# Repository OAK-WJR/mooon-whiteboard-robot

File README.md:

# MOOON: a robot that drives on a vertical whiteboard

MOOON (the project folder is called WhiteBoardBot) is a small robot with three
omni wheels that holds itself to a **vertical magnetic whiteboard** with
magnets. It can hold still against gravity, sweep the whole board in lanes,
find ink with a camera and erase it, and draw with a pen. It runs on circuit
boards I designed and on ESP32-C6 firmware. A phone camera facing the board
measures where the robot really is and sends corrections over Wi-Fi.

*2026-10-27: the robot from above, on the purple base board (v2.6) that I
designed.*

> This repository keeps the real git history of the project from June 2026
> (when it moved into git) to today, filtered for review: raw logs, videos,
> vendor models and design backups were removed from every commit, and the
> final commit adds my uncommitted work from Oct 28–31, 2026. The Feb–Apr 2026
> work (v1 board, first chassis) appears only as images and netlists. The
> unfiltered repository, with about 1 GB of raw logs and videos, stays private.

## Demo

*2026-10-26: full-board coverage run on a 35 × 23 in whiteboard (writable
area 33.5 × 21.5 in), 4× speed. Red: path measured by the camera. Blue:
planned area. 13 lanes in 96.6 s; it came back to its start within 0.2 mm.*

| Before erasing | After erasing | Drawing "67" |
|---|---|---|
|  |  |  |
| 2026-10-28 22:35: 130 cm² of ink | 2026-10-28 ≈22:40: board clean | 2026-10-31: one continuous pen line |

Video: the MOOON part of the video in my MIT Maker Portfolio shows the erase
run and the "67" drawing. Raw videos are not stored in this repository.

## How it works

```
 iPhone camera (Continuity Camera) ─> Mac: OpenCV finds 4 red corner tapes
                                     and the robot's LCD beacon
                                          │ position fixes over Wi-Fi
                                          ▼
 ┌────────────────────────── robot ──────────────────────────┐
 │ ESP32-C6-LCD-1.47 module      <- c6_wall firmware          │
 │   └─ adapter PCB (v2, my design)                           │
 │        └─ base PCB (v2.6, my design): 3 H-bridges, 2S LiPo │
 │             └─ 3 N20 gearmotors with encoders,             │
 │                38 mm omni wheels at 120°, magnets          │
 └────────────────────────────────────────────────────────────┘
```

- **Holding on the wall.** Each wheel is a position servo. The integral term
  is never reset, because it holds the torque that keeps the robot up against
  gravity. When idle or after a fault, the motor drivers brake.
  ([`c6_wall/include/wbb_core.h`](c6_wall/include/wbb_core.h))
- **Slip.** The wheels slip on the glossy board, and the encoders cannot see
  that. Camera measurements gave a slip factor for each direction, and the
  firmware corrects its odometry with them.
- **Camera referee.** Four red tapes give the board's corners; the robot's LCD
  shows a cyan/magenta beacon that gives its position and heading. Each fix is
  matched to the robot's odometry history to cancel the camera delay.
  ([`c6_wall/tools/vision.py`](c6_wall/tools/vision.py))
- **Erasing.** The eraser is the felt under the middle magnet. The camera
  finds the ink, the planner covers it with left-right lanes 1.6 cm apart, and
  the robot repeats until nothing is left, then does a fine wipe.
  ([`c6_wall/tools/clean_dirty.py`](c6_wall/tools/clean_dirty.py))
- **Drawing.** The pen cannot lift, so "67" is one continuous path of 30
  points, driven with live camera corrections.
  ([`c6_wall/tools/draw_digits.py`](c6_wall/tools/draw_digits.py))

More detail and the full timeline of what failed and what changed:
[`docs/design-history/`](docs/design-history/),
[`hardware/README.md`](hardware/README.md),
[`c6_wall/README.md`](c6_wall/README.md).

## Build and run

**Hardware needed:** the robot (Waveshare ESP32-C6-LCD-1.47, my adapter v2 and
base v2.6 boards, 3 N20 encoder gearmotors, 38 mm omni wheels, magnets, 2S
LiPo), a magnetic whiteboard with red tape on its four corners, a Mac with an
iPhone as Continuity Camera for the camera tools, and a USB-C cable for the
first flash.

```bash
# PlatformIO needs Python 3.10 or newer (macOS's built-in python3 is 3.9).
# The first build downloads the ESP32 toolchain into ./.platformio
python3.13 -m venv .venv && .venv/bin/pip install platformio
cd c6_wall
../.venv/bin/pio run                  # build the firmware
../.venv/bin/pio run -t upload        # first install over USB
python3 tools/ota.py                  # later updates over Wi-Fi

# desktop simulation test of the control core (no hardware needed)
c++ -std=c++17 -Iinclude tests/sim_test.cpp -o /tmp/sim && /tmp/sim

# camera tools (system python3 with OpenCV)
python3 -m pip install opencv-python numpy
python3 tools/clean_dirty.py scan     # find ink and draw the plan, robot does not move
```

Checked on 2026-11-01 on macOS from this snapshot: `pio run` builds
(`[SUCCESS]`, RAM 22.0 %, flash 45.5 %), and the simulation test prints
`ALL PASSED`. The robot joins Wi-Fi from its own web page; its hotspot
password is random and shown on the LCD (see
[`c6_wall/README.md`](c6_wall/README.md)). No Wi-Fi password is stored in the
source.

The firmware for the next, not-yet-built controller board can also be built
and checked against the board's netlist:

```bash
.venv/bin/pip install -r scripts/requirements-control.txt
.venv/bin/pio run -e top_board_v2_kiss_c6
python3 control_tests/verify_kiss_c6.py   # pins vs EasyEDA netlist, host-side tests
```

## Repository layout

| Path | What it is | State |
|---|---|---|
| [`c6_wall/`](c6_wall) | Current robot firmware, desktop simulation test, camera, erase and drawing tools, [key run logs](c6_wall/results) | **current** |
| [`hardware/`](hardware) | Board designs: `top_board_v2/motor_controller.epro2` (EasyEDA Pro project with the adapter, the base board and the next controller board), netlist exports, the v1 base board netlist, September KiCad sources | current + history |
| [`docs/`](docs) | Design history with dated pictures, demo media, older reports | |
| [`c6_drive/`](c6_drive) | September firmware: Wi-Fi driving, system ID, MuJoCo simulation | archived |
| [`src/`](src), [`include/`](include), [`platformio.ini`](platformio.ini), [`control_tests/`](control_tests), [`scripts/`](scripts) | Spring ESP32 firmware, the August C6 port, firmware and host tests for unbuilt top-board versions, host tools | mostly archived |
| [`c6_selftest/`](c6_selftest), [`testboard_selftest/`](testboard_selftest), [`c6-test/`](c6-test), [`usb_diagnostics/`](usb_diagnostics) | Bring-up and diagnostic firmware | archived |
| [`third_party/`](third_party) | Patched copy of Espressif's ESP-IDF I2C driver (Apache-2.0) | |

Many September notes were written in Chinese at the time and translated into
English in November 2026. Some notes in archived folders link to raw
reports, previews or review files that are only in the full-history
repository.

## Results and limits

What worked on the real robot:
- Holding still on the vertical board, and full-board coverage with camera
  correction (13 lanes in 96.6 s, back to start within 0.2 mm).
- Live camera corrections matter: for 8 cm out-and-back moves at erase speed,
  the average end error was 0.48 cm without corrections and 0.03 cm with them
  (2026-10-28, [`sysid-motion-run.log`](c6_wall/results/sysid-motion-run.log)).
- Autonomous erase (2026-10-28): ink area 130 → 2.31 cm² after pass 1 and
  1.69 cm² after pass 2; after pass 3 and a fine wipe, the final camera check
  found 0 cm² of ink.
  ([`c6_wall/results/`](c6_wall/results))
- Drawing "67" (2026-10-31): 15 cm tall, 30 points; the camera-measured miss
  at each point was 0.17 mm on average and 0.43 mm at most.
- Wi-Fi firmware updates that roll back by themselves if the new image fails.

Honest limits:
- The accuracy depends on the camera. Encoders alone cannot see the wheels
  slip, and without corrections the robot drifts.
- Spinning on the wall caused two power resets and the robot fell both times,
  so erasing while spinning is paused.
- The pen is fixed to the chassis and cannot lift.
- The single integrated controller board (`top_board_v2_logic`: native USB,
  on-board 2S charging, current sensing) is designed but **not built or
  tested**. Its firmware runs only host-side checks, with motion disabled.
- Several earlier top-board designs (September 2026) were dropped for
  complexity or cost and were never ordered.
- All tests were on one 35 × 23 in whiteboard at home.

## Credits

**My work (Jiarui "Jerry" Wu).** The idea and the requirements; the
mechanical design in Onshape; the v1 base board schematic and layout; the
v2.6 base board and the layout of the v2.6 adapter board, and the September
fix of the adapter's M1 header, which had been placed rotated 180°;
assembling, soldering and debugging the robot; running the tests on the real
robot. I proposed using my phone camera as a referee to
measure wheel slip, measured slip by hand, chose the erase approach (find the
dirty spots, plan a path, erase with the felt under the magnet), asked for the
fine wipe, and chose the stroke order for "67". I set the "keep it simple"
rules for the boards and checked the pin assignments before each order.

**Code written by AI tools, from my designs and under my direction; I tested
and tuned it:**
- **Claude Code (Anthropic):** firmware changes in June 2026 (feed-forward,
  stiction); the first draft of the v2.6 adapter board schematic through the
  EasyEDA API in July (I revised it and laid out the board); pre-order design reviews;
  the September self-test firmware; the October wall firmware and tools in
  `c6_wall/` (Wi-Fi updates, coverage planner, camera referee, slip
  identification, erasing, drawing, demo cutting); most of the schematic clean-up,
  routing and checks of the unbuilt `top_board_v2_logic` board in EasyEDA
  from my requirements (Oct 27–30), starting from the Codex KiCad draft
  below; its review firmware and tests (Oct 2026).
- **OpenAI Codex:** the September top-board explorations (KiCad, never built)
  and the September firmware in `c6_drive/` (Wi-Fi driving, web page,
  calibration, system ID, MuJoCo simulation).
- **Cursor:** much of the spring 2026 firmware and test tools.
- **ChatGPT:** help reading error screens and wiring motor drivers in
  February 2026.

**Existing open-source work and parts.** Espressif ESP-IDF I2C driver
(Apache-2.0, patched copy in `third_party/` with its licence); Arduino-ESP32
through the pioarduino PlatformIO platform; ArduinoJson (MIT); Adafruit
ST7735/ST7789 library (MIT); OpenCV; MuJoCo (Apache-2.0) for the September
simulation; EasyEDA Pro and KiCad, with some symbols and footprints from the
EasyEDA/LCSC part library and the `ESP32-C6-MINI-1` footprint copied from the
KiCad footprint library (CC-BY-SA 4.0 with the KiCad library exception); the Waveshare ESP32-C6-LCD-1.47 module (bought).
This is a personal project; no teammates' code is included.

## License

- Software: [MIT](LICENSE).
- Hardware design files in [`hardware/`](hardware): [CERN-OHL-P-2.0](hardware/LICENSE).
- [`third_party/esp_idf_i2c_no_clear`](third_party/esp_idf_i2c_no_clear):
  Apache-2.0 (Espressif).

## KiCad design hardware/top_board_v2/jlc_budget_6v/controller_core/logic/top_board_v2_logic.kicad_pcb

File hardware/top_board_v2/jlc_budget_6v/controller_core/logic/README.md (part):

# Top board: MINI schematic and two-layer layout review draft

> **Superseded (2026-10-27).** The current board is `top_board_v2_logic` in the EasyEDA project (same name, see [hardware/README.md](../../../../README.md)): on-board IP2326 charging, native USB (CH343G removed on 2026-10-29), VBAT divider plus INA180 motor current sensing. Current pins follow [`include/board_profile_kiss_c6.h`](../../../../../include/board_profile_kiss_c6.h) and the EasyEDA netlist; the firmware notes are in [FIRMWARE.md](FIRMWARE.md). The six-page KiCad drawing, pin table, routing and verification records on this page are all 2026-09 history; "current" and "latest" in the text refer to that time.

The current budget only covers **five top PCBs, the components on them and soldered finished boards**, total target ¥30, cap ¥50. The current candidate does not meet the budget, and routing and manufacturing verification are not done.

- [KiCad project](top_board_v2_logic.kicad_pro) / [PCB](top_board_v2_logic.kicad_pcb) / [layout preview](preview/placement.png)
- [Six-page schematic PDF](top_board_v2_review.pdf) / [root schematic](top_board_v2_logic.kicad_sch)
- Pages: [index](preview/index.png), [controller](preview/controller.png), [USB recovery](preview/usb_recovery.png), [base board interfaces](preview/bottom_interfaces.png), [sensing](preview/voltage_sense.png), [power](preview/power_stage.png)
- [Actual netlist](logic.net.xml), [schematic verification](verification/report.json), [placement record](placement_report.json), [DRC](placement_drc.json), [top/bottom board registration](bottom_alignment.json), [firmware](FIRMWARE.md)

The schematic is **6 pages, 70 physical components, 246 physical pins, ERC 0 errors, 0 warnings**. The controller, USB auto recovery, the original base board interface, two dividers and two buck converters are merged; only one ARM pull-down, R24, is fitted. The base board's three H-bridges are still reused, and the top has no on-board charging or balancing.

## MCU and pins

The space review candidate changed to **ESP32-C6-MINI-1-N4 / C5736265**. In a conservative coarse-grid screening that kept the 19 through-hole contacts and the antenna keep-out, no position was found for the original WROOM; this is not a mathematical proof that it cannot be placed. The MINI trial placement fits in the existing board outline, but its global-site part number is **Standard Only, X-ray inspection required**, so the Economic assembly price cannot be reused. So this drawing is a space and wiring review candidate, and **has not become a low-cost final design**. [JLC part limits](https://jlcpcb.com/partdetail/ESPRESSIFINC-ESP32_C6_MINI_1N4/C5736265).

The MINI was checked independently against table 3-1 and the recommended land pattern in the [Espressif v1.5 manual](https://www.espressif.com/sites/default/files/documentation/esp32-c6-mini-1_mini-1u_datasheet_en.pdf), using 53 physical pin numbers and 61 native pad objects, including 9 ground pads that all belong to pin 49. The WROOM's 29-pin mapping cannot be reused. The MINI does not bring out GPIO10/11, so ARM changed to **GPIO14 / pin 19** and M0_BI to **GPIO23 / pin 29**; the firmware of that time was updated to match. The current firmware follows the new EasyEDA drawing: ARM is GPIO0 (pin 12), and GPIO14 is M2_FI.

2026-09 KiCad pins (superseded; now Motor1 22/23, 20/21, Motor2 14/7, 19/18, Motor3 1/6, 2/3):

| Physical motor | Top board → base board | FI / BI GPIO | Encoder A / B GPIO |
| --- | --- | --- | --- |
| Motor1 | M0 → H2 | 22 / 23 | 0 / 1 |
| Motor2 | M2 → H3 | 20 / 21 | 6 / 7 |
| Motor3 | M1 → H1 | 18 / 19 | 2 / 3 |

At that time UART TX16/RX17 mapped to module pins 31/30, and native USB GPIO12/13 were unused; now pins 31/30 are I2C_SCL (GPIO16) and IR_EN_N (GPIO17), and GPIO12/13 are the native USB console. The physical pins for GPIO4/5 sensing are 9/10. The GPIO15 pull-up and the encoder use of GPIO6/7 depend on the default JTAG selection and cannot cover arbitrary eFuse configurations. GPIO14 floats during chip reset, so an external 10k pull-down is added; this does not mean the actual motor power has been verified as off by default. [C6 chip datasheet](https://www.espressif.com/sites/default/files/documentation/esp32-c6_datasheet_en.pdf).

## Layout and interfaces

The PCB has two layers, 70 electrical footprints and 4 Ø2.4mm mounting holes, with **587 trace segments, 167 vias, two ground pours, 10 unconnected items**. Except for the four original base board mating headers, all electrical components are on the front. Placement coordinates come from the [hand placement table](../placement.json), and no autorouter was used; traces run in directions that are multiples of 30°. Ø6mm is currently reserved around the holes; the actual fasteners and top bracket are not verified.

The 19 pad centers, sizes, hole sizes, angles and through-hole attributes of the four connectors are identical, item by item, to the original top board. PWR was renamed PWR1: pin 1 GND, pins 2/3/4 VMOT. M0.1 is the controller 3.3V, M1.1/M2.1 are GND. After the base board CAD is rotated by about 30° and translated, the max residual of the 19 matching points is **0.00103mm**, with no mirroring; the top board outline is inside the base board. This is a nominal 2D dimension check, not a real tolerance or 3D mating verification.

The latest DRC keeps **one M2/PWR1 assembly boundary overlap**; it was not masked. The placed components report no copper short/clearance errors, but with only the local copper above, this cannot represent the whole board being connected. Adjacent pads of U4's fixed footprint are 0.15mm apart, using a 0.15mm rule that only applies to U4's internal pads; normal copper clearance stays 0.2mm, milled edge clearance 0.3mm, and the module's edge ground pads are locally 0.2mm. These are based on the 1oz two-layer process and cannot be applied directly to 2oz. [JLC capabilities](https://jlcpcb.com/capabilities/pcb-capabilities/).

Since the user allowed "the same shape as the base board", the top board now uses the nominal outline of the registered base board shrunk inward by 0.05mm, about 69.23 × 60.15mm; the original 19 pads, hole sizes and angles are kept. This is a CAD inset, not a guaranteed finished-dimension tolerance. USB moved 2.5mm toward the new bottom edge; the MINI moved up 3.84mm, and the decoupling capacitors and TX series resistor moved with it. The space and selection basis is in the [screening record](../outline_fit_review/README.md).

The MINI antenna end sticks out about **5.5mm** past the top board. The nominal 2D overlap of the native all-copper-layer keep-out with both the top and bottom boards is 0; the original position had about 61.37mm² of overlap with the base board. The [projection check](antenna_projection.json) measured only about **0.046mm** from the keep-out to the lower board outline, and about **0.204mm** from the nearest module pad to the top board edge. The former is less than normal milling tolerance; **zero nominal overlap still does not mean the actual RF clearance passes**; manufacturing tolerance, stack height, fasteners and communication tests still need verification. [Manufacturer module layout guide](https://docs.espressif.com/projects/esp-hardware-design-guidelines/en/latest/esp32c6/pcb-layout-design.html#general-principles-of-pcb-layout-for-modules-positioning-a-module-on-a-base-board).

The 3.3V power area re-placed C7/C8, the feedback R/C and the enable resistor, kept the two SW segments, redrew FB, and added input, output, enable and ground return copper. In the [local close-up](preview/u4_supply_detail.png), C8 sits near U4's input pin and C7 moved above the inductor to avoid the original M0 through-hole pads; the feedback node stays on U4's left, the separate output sense is taken from C11, and the feedback ground returns separately to U4's ground pin via. The right-side back ground pour gives the input and output capacitors a return path. Basis: [TI TPS563252 layout guide §8.4](https://www.ti.com/lit/ds/symlink/tps563252.pdf); this still needs real-board dynamic and thermal verification.

In the earlier 3.3V stage, the KiCad native copper connection graph checked six connection groups: VIN, GND, VOUT, SW, FB and EN; temporary copies with the input trace or the output trace cut both detected the expected break, and the unconnected count rose from 174 at the time to 175. [Original check record of that stage](../archive/u5_before_supply/top_board_v2_logic.verification.json). This 6V stage keeps all those traces and vias and re-checks the six connectivity groups. The input diode to this area was connected in the later input routing stage, and the rest of the circuit is still not fully routed; the 3.3V load distribution was connected in the later controller power stage; **partial connectivity does not mean the regulator or the whole board works**. Later loads must not connect to the thin separate output sense branch.

In the 6V area, L2 was rotated 90°, and C14–C19, the feedback R/C, the EN pull-down R24 and the bleed R30 were re-placed; no components were added. The [6V close-up](preview/u5_supply_detail.png) shows the input decoupling, BST/SW, soft start, feedback, output capacitors and bleed connections. R24 has moved near U5's EN, and the MCU-to-EN connection was made in the later control routing stage. The separate output sense and bleed branches each come out from the via at C19's output end; R30's branch does not connect at the feedback divider node. The layout follows [TI TPS62933 §12.1](https://www.ti.com/lit/ds/symlink/tps62933.pdf) to shorten the key pin paths; thermal and dynamic behavior with the current 1oz copper, the base board's large capacitors and the real load are not verified.

The USB interface finished this round's local hand routing: U2 was turned and moved close to the Type-C connector, the data lines pass through the protection pads, and the contacts for both plug orientations, the CC pull-downs, the USB-side VBUS and the decoupling connections were checked. 67 segments and 14 vias were added, with no new components. The [USB close-up](preview/usb_interface_detail.png) and the [full check notes](USB_ROUTING_REVIEW.md) record the locating hole avoidance, capacitor positions and unfinished conditions.

Next, the local routing of auto reset and serial was done: the EN R/C moved to the same side as the controller, and DTR/RTS, GPIO9, GPIO8 and UART TX/RX were connected per the existing netlist. 85 segments and 18 vias were added, with no new components. The [reset control area](preview/reset_control_detail.png), [controller EN/BOOT area](preview/mcu_reset_detail.png) and [full notes](RESET_ROUTING_REVIEW.md) record the specific connections and the remaining power conditions.

The controller power stage connected all 22 MAIN_3V3 net pads, including the controller, the VIO of the USB serial chip, the boot and encoder pull-ups, and the base board encoder power. C5/C6 form a local decoupling loop, and all 30 physical ground pads of the controller join the common ground; two BOOT segments made way for the short bridges where the power changes layers. The [controller power close-up](preview/mcu_supply_detail.png) and the [full notes for that round](MCU_SUPPLY_REVIEW.md) record the 66 new segments, 32 new vias and four component adjustments.

Next, GPIO14 to U5 EN, the GPIO15 pull-up, the full M2 FI/BI paths, and the six pull-down returns of the three interfaces were connected. R25 moved near the controller and R20/R21 avoid the header holes and power capacitors; the schematic and BOM did not change. The four old local ground pour definitions were replaced by the full-board back-side ground, and the module front-side ground was kept; after refilling there were no isolated copper errors. The [control area close-up](preview/motor_controls_detail.png) and [stage notes](MOTOR_CONTROL_ROUTING_REVIEW.md) record these changes.

Earlier, the six encoder interfaces were connected to their pull-up resistors, and the two M2 encoder A/B paths to the controller were completed. At that time the four M0/M1 encoder controller leads were still unconnected. All component positions are unchanged; GPIO15, M2_FI and BOOT were rerouted locally and one ground via was moved, to make way for the encoder breakout. 57 segments and 11 vias were added, replacing 10 old segments and 2 vias; the outer bends use 30°/60° turns. The [encoder close-up](preview/encoder_links_detail.png) and [stage notes](ENCODER_ROUTING_REVIEW.md) record these changes.

Next, the M1 encoder A/B paths to controller GPIO2/3 were completed; at that time the two M0 encoder controller leads were still pending. All footprint positions are unchanged; the controller's local 3.3V branch was rerouted at its original width, the C4 ground via and the ARM local path made way, and two explicit ground returns were added on the bottom side of the controller. 40 segments and 16 vias were added, replacing 6 segments and 3 vias. The [left encoder close-up](preview/left_encoder_pair_detail.png) and [stage notes](LEFT_ENCODER_ROUTING_REVIEW.md) record these changes.

Next, the M0 encoder A/B paths to GPIO0/1 were completed, so all six encoder signals of the three groups on the top are connected. All footprint positions are unchanged; the R25 power branch, the U4 input copper and the C8 ground via were adjusted locally, the small M2 encoder A bridge inside the module was rerouted, and the bottom-side ground return was completed. 78 segments and 22 vias were added, replacing 12 segments and 7 vias. The [right encoder close-up](preview/right_encoder_pair_detail.png) and [full notes](RIGHT_ENCODER_ROUTING_REVIEW.md) record the paths of this stage.

Next, the M0 FI/BI paths to GPIO22/23 were completed, running along the right side in 30°/60° directions to avoid the power area. The C5/C6 power bridge moved to the back side, keeping the two power input vias and the 0.65mm width; an explicit controller ground return was added near C6. 38 segments and 12 vias were added, replacing six segments and two vias; all footprints, the schematic, BOM and firmware are unchanged. The [right control line close-up](preview/right_motor_pair_detail.png) and [full notes](RIGHT_MOTOR_ROUTING_REVIEW.md) record the paths of this stage.

Next, the VMOT distribution from C19 to the three power contacts of PWR1, and the four ground ends of C20/R34 and C21/R36, were connected. 12 segments and two ground vias were added, and all old copper, footprints, the schematic, BOM and firmware are kept. The new power copper is 1.2mm; the original 1.0mm segment from L2 to C19 is unchanged; loads do not connect to the thin feedback and bleed branches. The [power distribution close-up](preview/vmot_distribution_detail.png) and [full notes](VMOT_DISTRIBUTION_REVIEW.md) record the paths of this stage.

This round connected USB VBUS to D1 and the D1/D2 cathodes to the U4 input, and added a ground jumper near U4. 21 segments and nine vias were added; no old copper was removed and no footprints, BOM or firmware were changed. The new power trace is 0.8mm and takes power directly from the existing via of the USB contacts; D2's battery-side input is still not connected. The [input path close-up](preview/logic_input_detail.png) and [full notes](LOGIC_INPUT_ROUTING_REVIEW.md) record the current paths.

The [current native copper connection report](top_board_v2_logic.verification.json) confirms that the USB and power OR nets are connected, and that all 74 physical ground pads, 22 MAIN_3V3 pads, nine VMOT pads, the M0/M2 control lines and the six encoder lines stay connected. The 246 pin nets, 19 mating contacts, all 74 footprints, 724 old copper records and the pour/keep-out definitions were all checked. Eight open-circuit copies detected the matching breaks, with the unconnected count rising from 10 to 11; in another copy, after deleting the seven thin CH343 back-side power segments, the USB contacts still connect to D1, the CH343's two power inputs disconnect as expected, and the unconnected count is 12. The diode K/A pins match the actual XML netlist; this does not prove that the real reverse leakage and plug/unplug switching pass. The main board still has the original M2/PWR1 assembly boundary issue.

The [remaining connection details](remaining_connections.json) include the two control lines from M1 to the controller, three connections for each of the two sensing channels, and two connections on the battery input net. Copper connection checks cannot prove actual USB, default-off, startup timing, power dynamics or wireless stability.

## Verification and open items

The native netlist check covers all 246 physical pins, the 19 contacts, USB/EN/BOOT, the power sub-sheets and the manufacturer's module pads; all seven deliberately broken controls were detected. The original USB subcircuit's 72 DC and 3 timing simulations only cover that subcircuit, and the local RC simulation of the power supply is not a closed-loop regulator stability simulation either.

Added [24 DTR startup bias simulations](usb_startup_review/README.md): after the supply reaches 3.3V, the existing external pull-up keeps a sufficient model high level; a control with a wrong pull-down added detects insufficient margin; no parts were added as a result. The sampling instant, actual slow ramp/undervoltage and whole-board USB behavior are still not verified. The [wireless power policy](WIRELESS_POWER.md) is implemented: it starts wireless based on a valid voltage and auto-resets after power fails; the USB current budget and suspend current still need whole-board verification.

On 2026-09-09 the firmware **passed 73 offline checks and the two C6/R3 cross-compiles**; the logs and reports of that time have been overwritten by the current firmware verification, see git history and [FIRMWARE.md](FIRMWARE.md#verification). Motion is still forbidden by `BOARD_POWER_UNREVIEWED`; there has been no flashing, USB enumeration, wireless or loaded measurement.

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
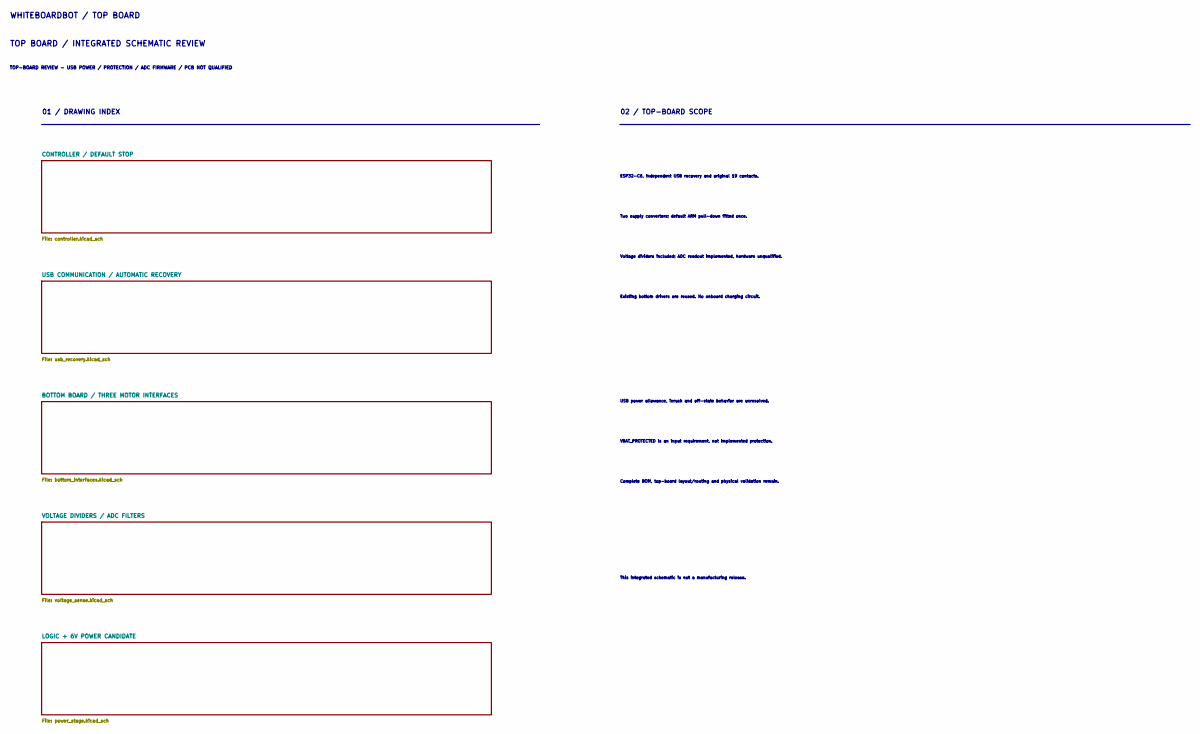
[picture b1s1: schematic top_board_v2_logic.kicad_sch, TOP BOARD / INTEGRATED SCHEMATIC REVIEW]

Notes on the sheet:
WHITEBOARDBOT / TOP BOARD
TOP BOARD / INTEGRATED SCHEMATIC REVIEW
TOP-BOARD REVIEW - USB POWER / PROTECTION / ADC FIRMWARE / PCB NOT QUALIFIED
01 / DRAWING INDEX
02 / TOP-BOARD SCOPE
ESP32-C6, independent USB recovery and original 19 contacts.
Two supply converters; default ARM pull-down fitted once.
Voltage dividers included; ADC readout implemented, hardware unqualified.
Existing bottom drivers are reused. No onboard charging circuit.
USB power allowance, inrush and off-state behavior are unresolved.
VBAT_PROTECTED is an input requirement, not implemented protection.
Complete BOM, top-board layout/routing and physical validation remain.
This integrated schematic is not a manufacturing release.

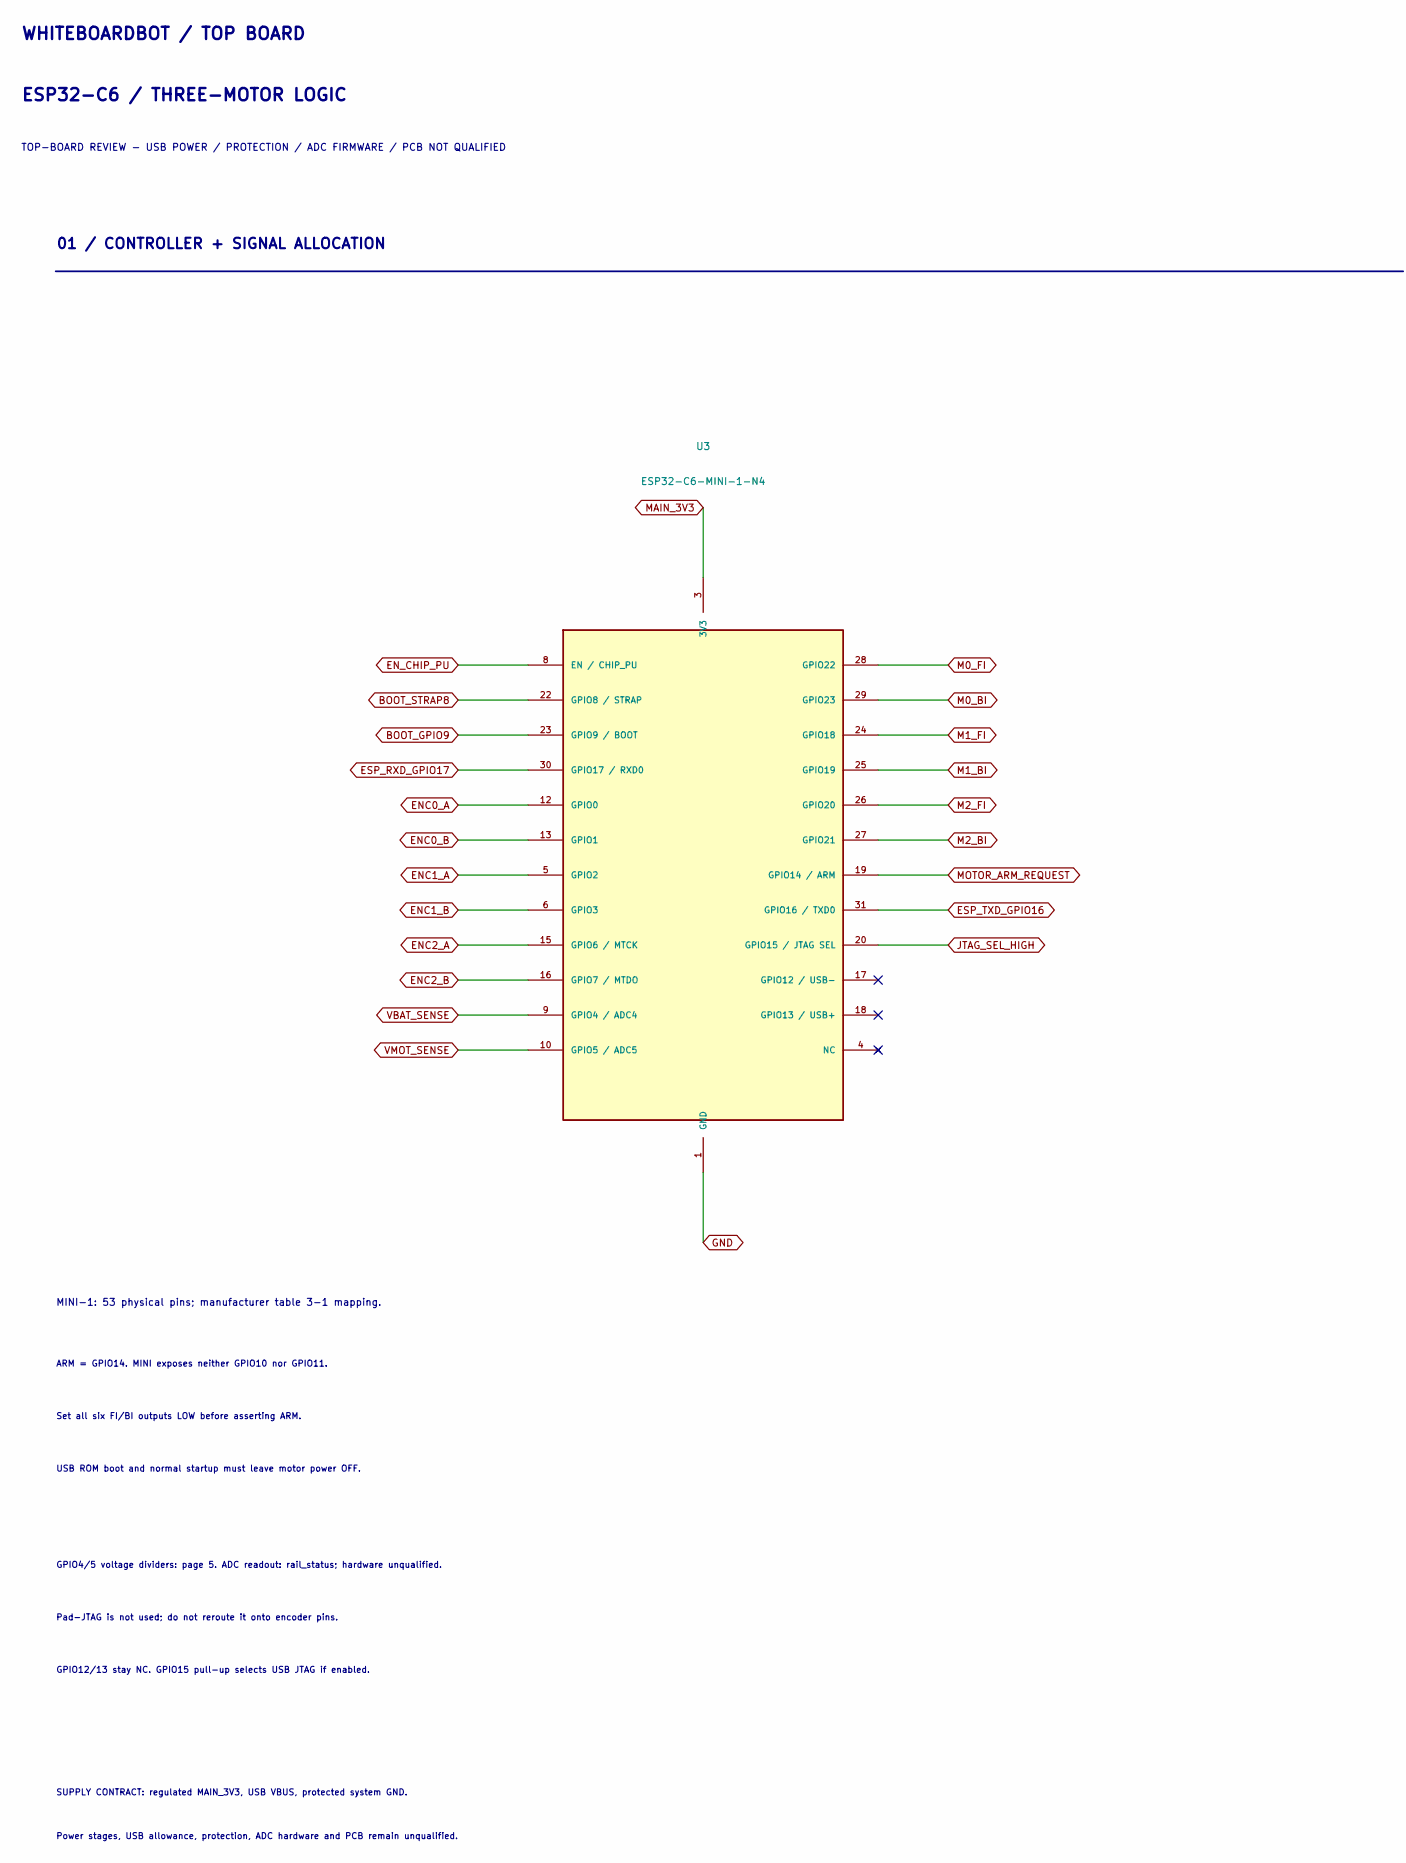
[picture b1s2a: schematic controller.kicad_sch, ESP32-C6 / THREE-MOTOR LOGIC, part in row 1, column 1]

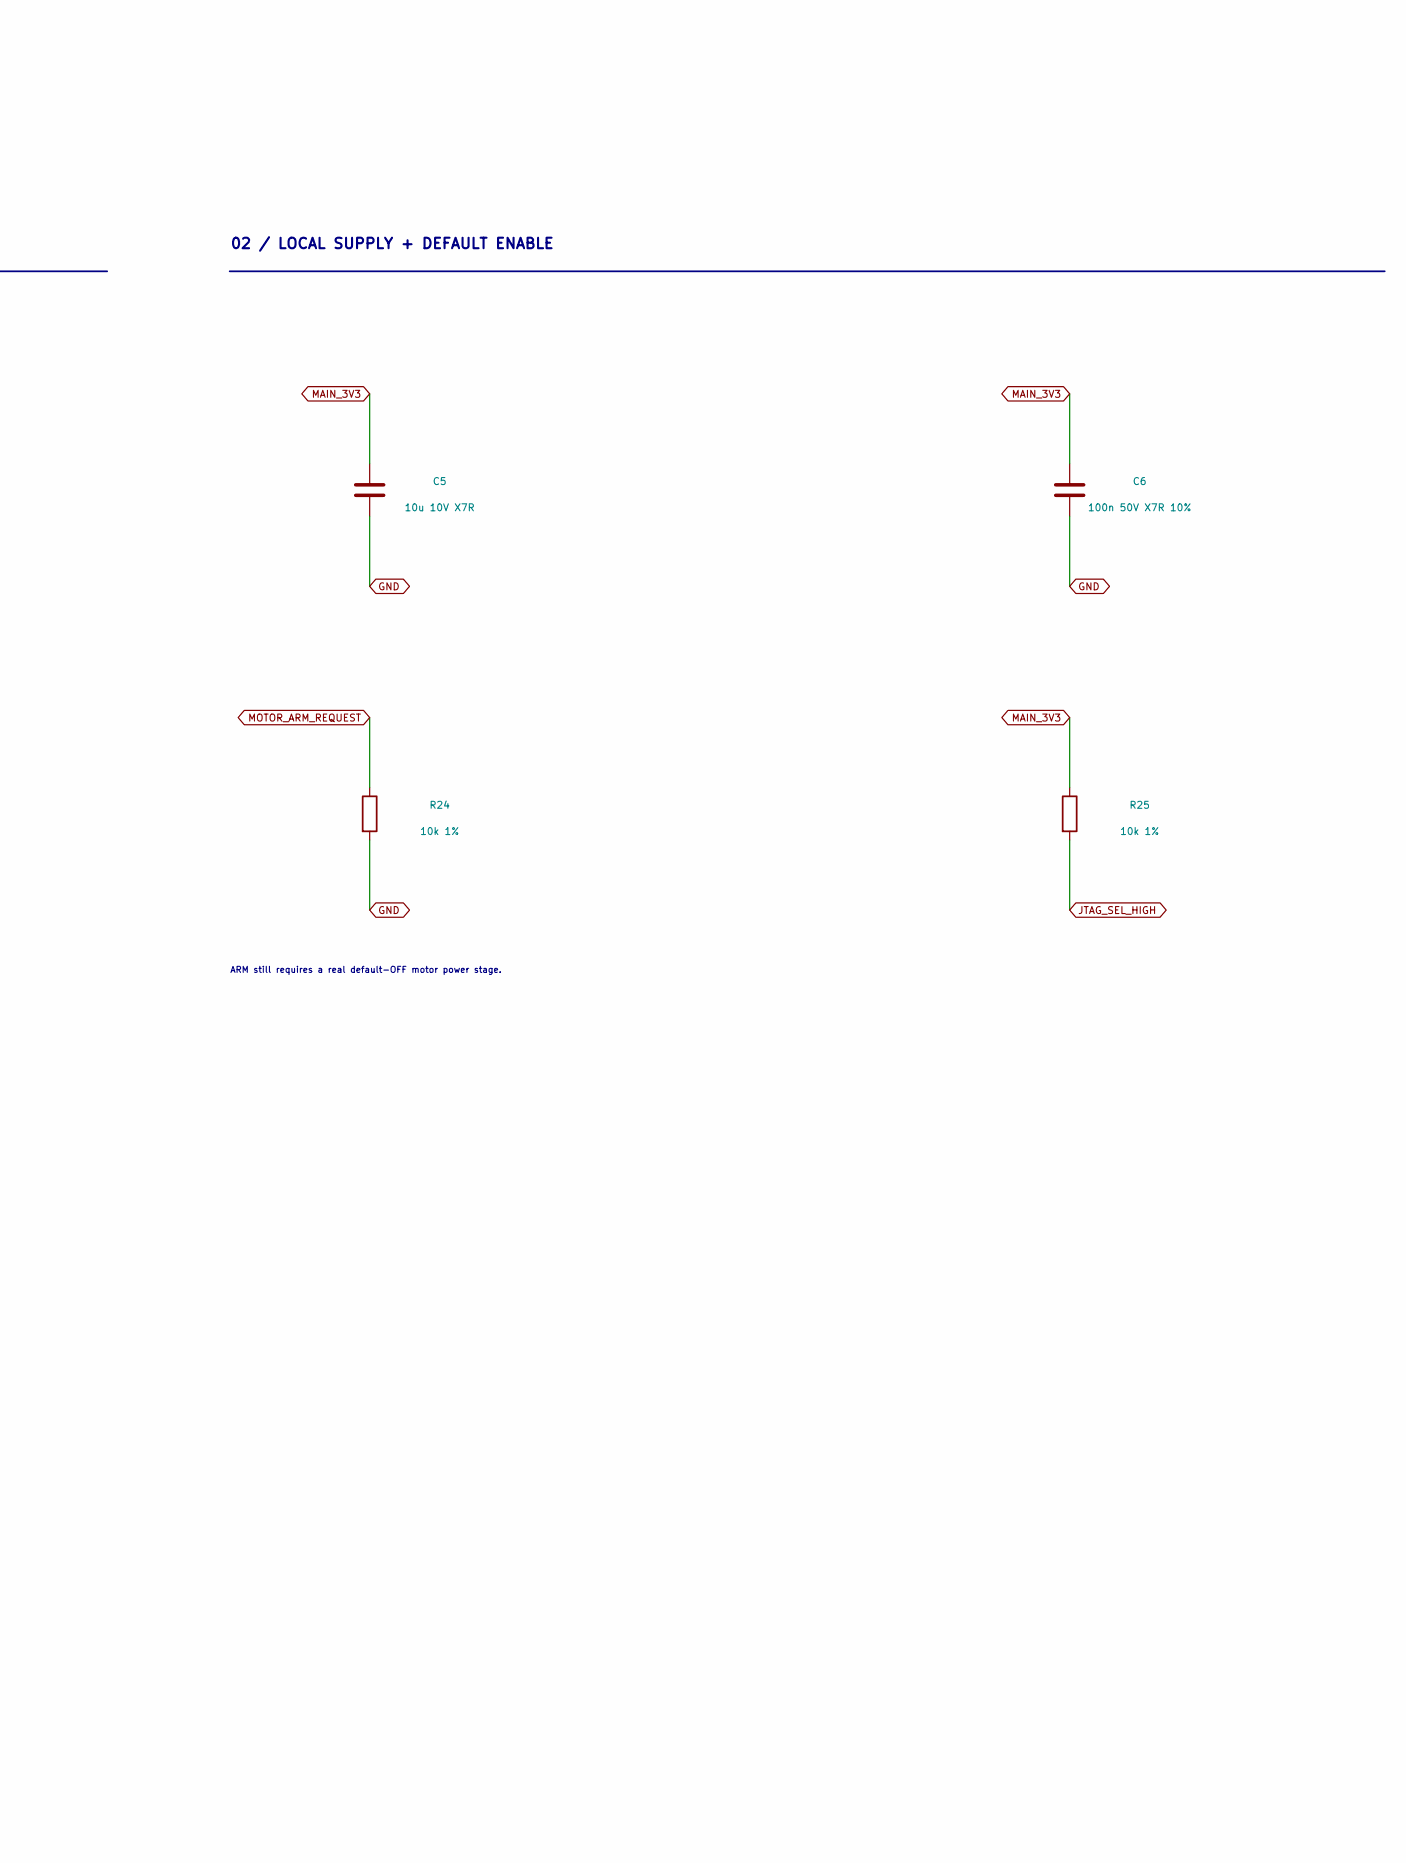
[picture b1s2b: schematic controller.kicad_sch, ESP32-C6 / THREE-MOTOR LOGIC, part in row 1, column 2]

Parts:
C5: 10u 10V X7R; C_0805_2012Metric
C6: 100n 50V X7R 10%; C_0603_1608Metric; mpn CC0603KRX7R9BB104; LCSC C14663
R24, R25: 10k 1%; R_0603_1608Metric; mpn 0603WAF1002T5E; LCSC C25804
U3: ESP32-C6-MINI-1-N4; ESP32-C6-MINI-1; LCSC C5736265

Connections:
BOOT_GPIO9: U3.23 (GPIO9 / BOOT); also elsewhere on the board
BOOT_STRAP8: U3.22 (GPIO8 / STRAP); also elsewhere on the board
ENC0_A: U3.12 (GPIO0); also elsewhere on the board
ENC0_B: U3.13 (GPIO1); also elsewhere on the board
ENC1_A: U3.5 (GPIO2); also elsewhere on the board
ENC1_B: U3.6 (GPIO3); also elsewhere on the board
ENC2_A: U3.15 (GPIO6 / MTCK); also elsewhere on the board
ENC2_B: U3.16 (GPIO7 / MTDO); also elsewhere on the board
EN_CHIP_PU: U3.8 (EN / CHIP_PU); also elsewhere on the board
ESP_RXD_GPIO17: U3.30 (GPIO17 / RXD0); also elsewhere on the board
ESP_TXD_GPIO16: U3.31 (GPIO16 / TXD0); also elsewhere on the board
GND: C5.2, C6.2, R24.2, U3.1 (GND), U3.2 (GND), U3.11 (GND), U3.14 (GND), U3.36 (GND), U3.37 (GND), U3.38 (GND), U3.39 (GND), U3.40 (GND), U3.41 (GND), U3.42 (GND), U3.43 (GND), U3.44 (GND), U3.45 (GND), U3.46 (GND), U3.47 (GND), U3.48 (GND), U3.49 (GND), U3.50 (GND), U3.51 (GND), U3.52 (GND), U3.53 (GND); also elsewhere on the board
JTAG_SEL_HIGH: R25.2, U3.20 (GPIO15 / JTAG SEL)
M0_BI: U3.29 (GPIO23); also elsewhere on the board
M0_FI: U3.28 (GPIO22); also elsewhere on the board
M1_BI: U3.25 (GPIO19); also elsewhere on the board
M1_FI: U3.24 (GPIO18); also elsewhere on the board
M2_BI: U3.27 (GPIO21); also elsewhere on the board
M2_FI: U3.26 (GPIO20); also elsewhere on the board
MAIN_3V3: C5.1, C6.1, R25.1, U3.3 (3V3); also elsewhere on the board
MOTOR_ARM_REQUEST: R24.1, U3.19 (GPIO14 / ARM); also elsewhere on the board
VBAT_SENSE: U3.9 (GPIO4 / ADC4); also elsewhere on the board
VMOT_SENSE: U3.10 (GPIO5 / ADC5); also elsewhere on the board

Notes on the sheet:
WHITEBOARDBOT / TOP BOARD
ESP32-C6 / THREE-MOTOR LOGIC
TOP-BOARD REVIEW - USB POWER / PROTECTION / ADC FIRMWARE / PCB NOT QUALIFIED
01 / CONTROLLER + SIGNAL ALLOCATION
MINI-1: 53 physical pins; manufacturer table 3-1 mapping.
ARM = GPIO14. MINI exposes neither GPIO10 nor GPIO11.
Set all six FI/BI outputs LOW before asserting ARM.
USB ROM boot and normal startup must leave motor power OFF.
GPIO4/5 voltage dividers: page 5. ADC readout: rail_status; hardware unqualified.
Pad-JTAG is not used; do not reroute it onto encoder pins.
GPIO12/13 stay NC. GPIO15 pull-up selects USB JTAG if enabled.
02 / LOCAL SUPPLY + DEFAULT ENABLE
ARM still requires a real default-OFF motor power stage.
SUPPLY CONTRACT: regulated MAIN_3V3, USB VBUS, protected system GND.
Power stages, USB allowance, protection, ADC hardware and PCB remain unqualified.

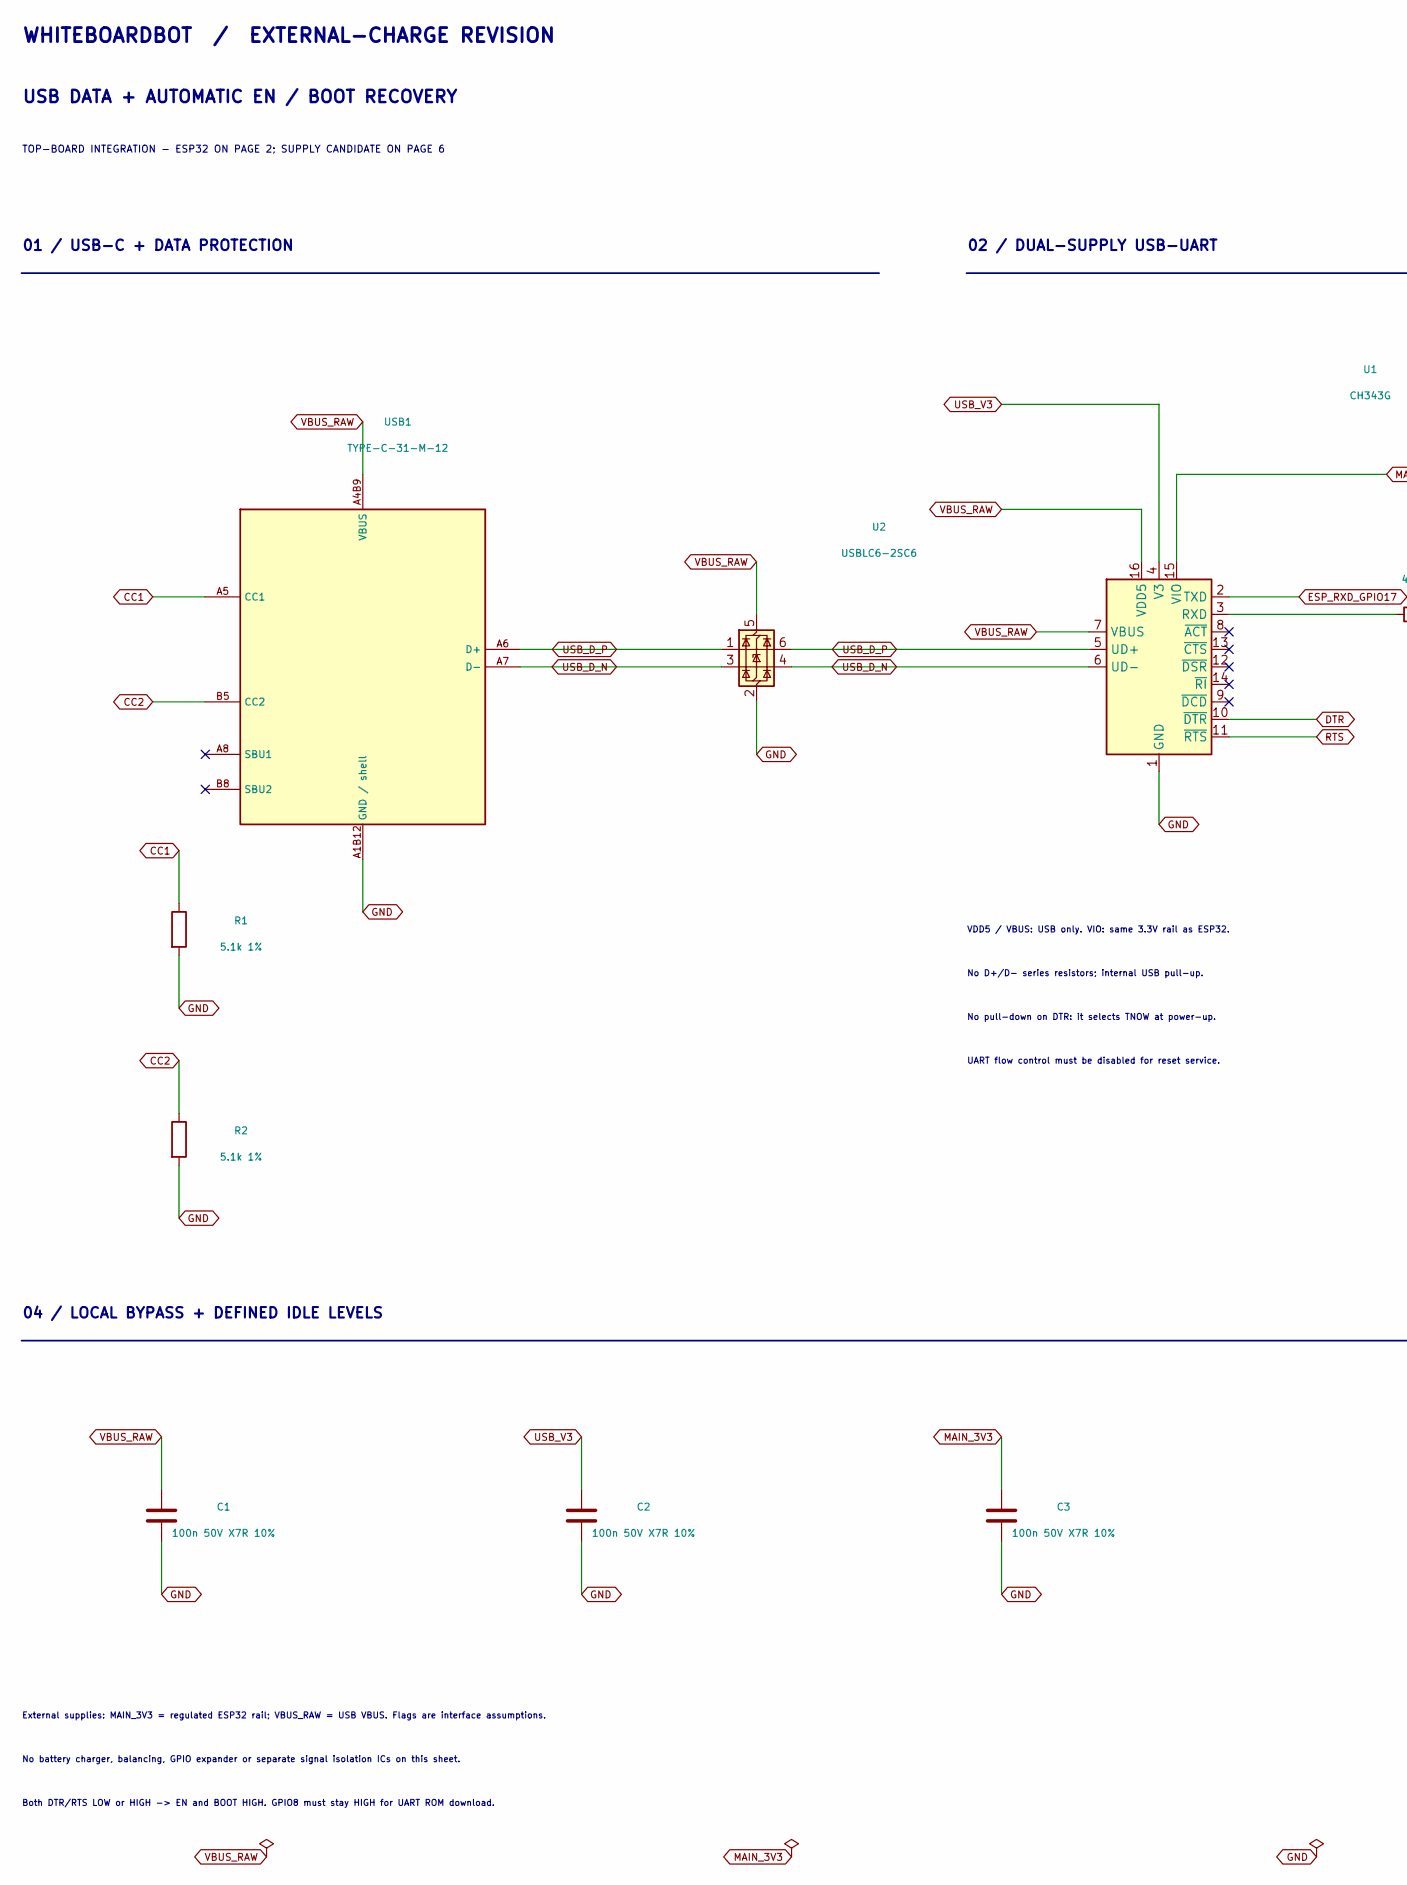
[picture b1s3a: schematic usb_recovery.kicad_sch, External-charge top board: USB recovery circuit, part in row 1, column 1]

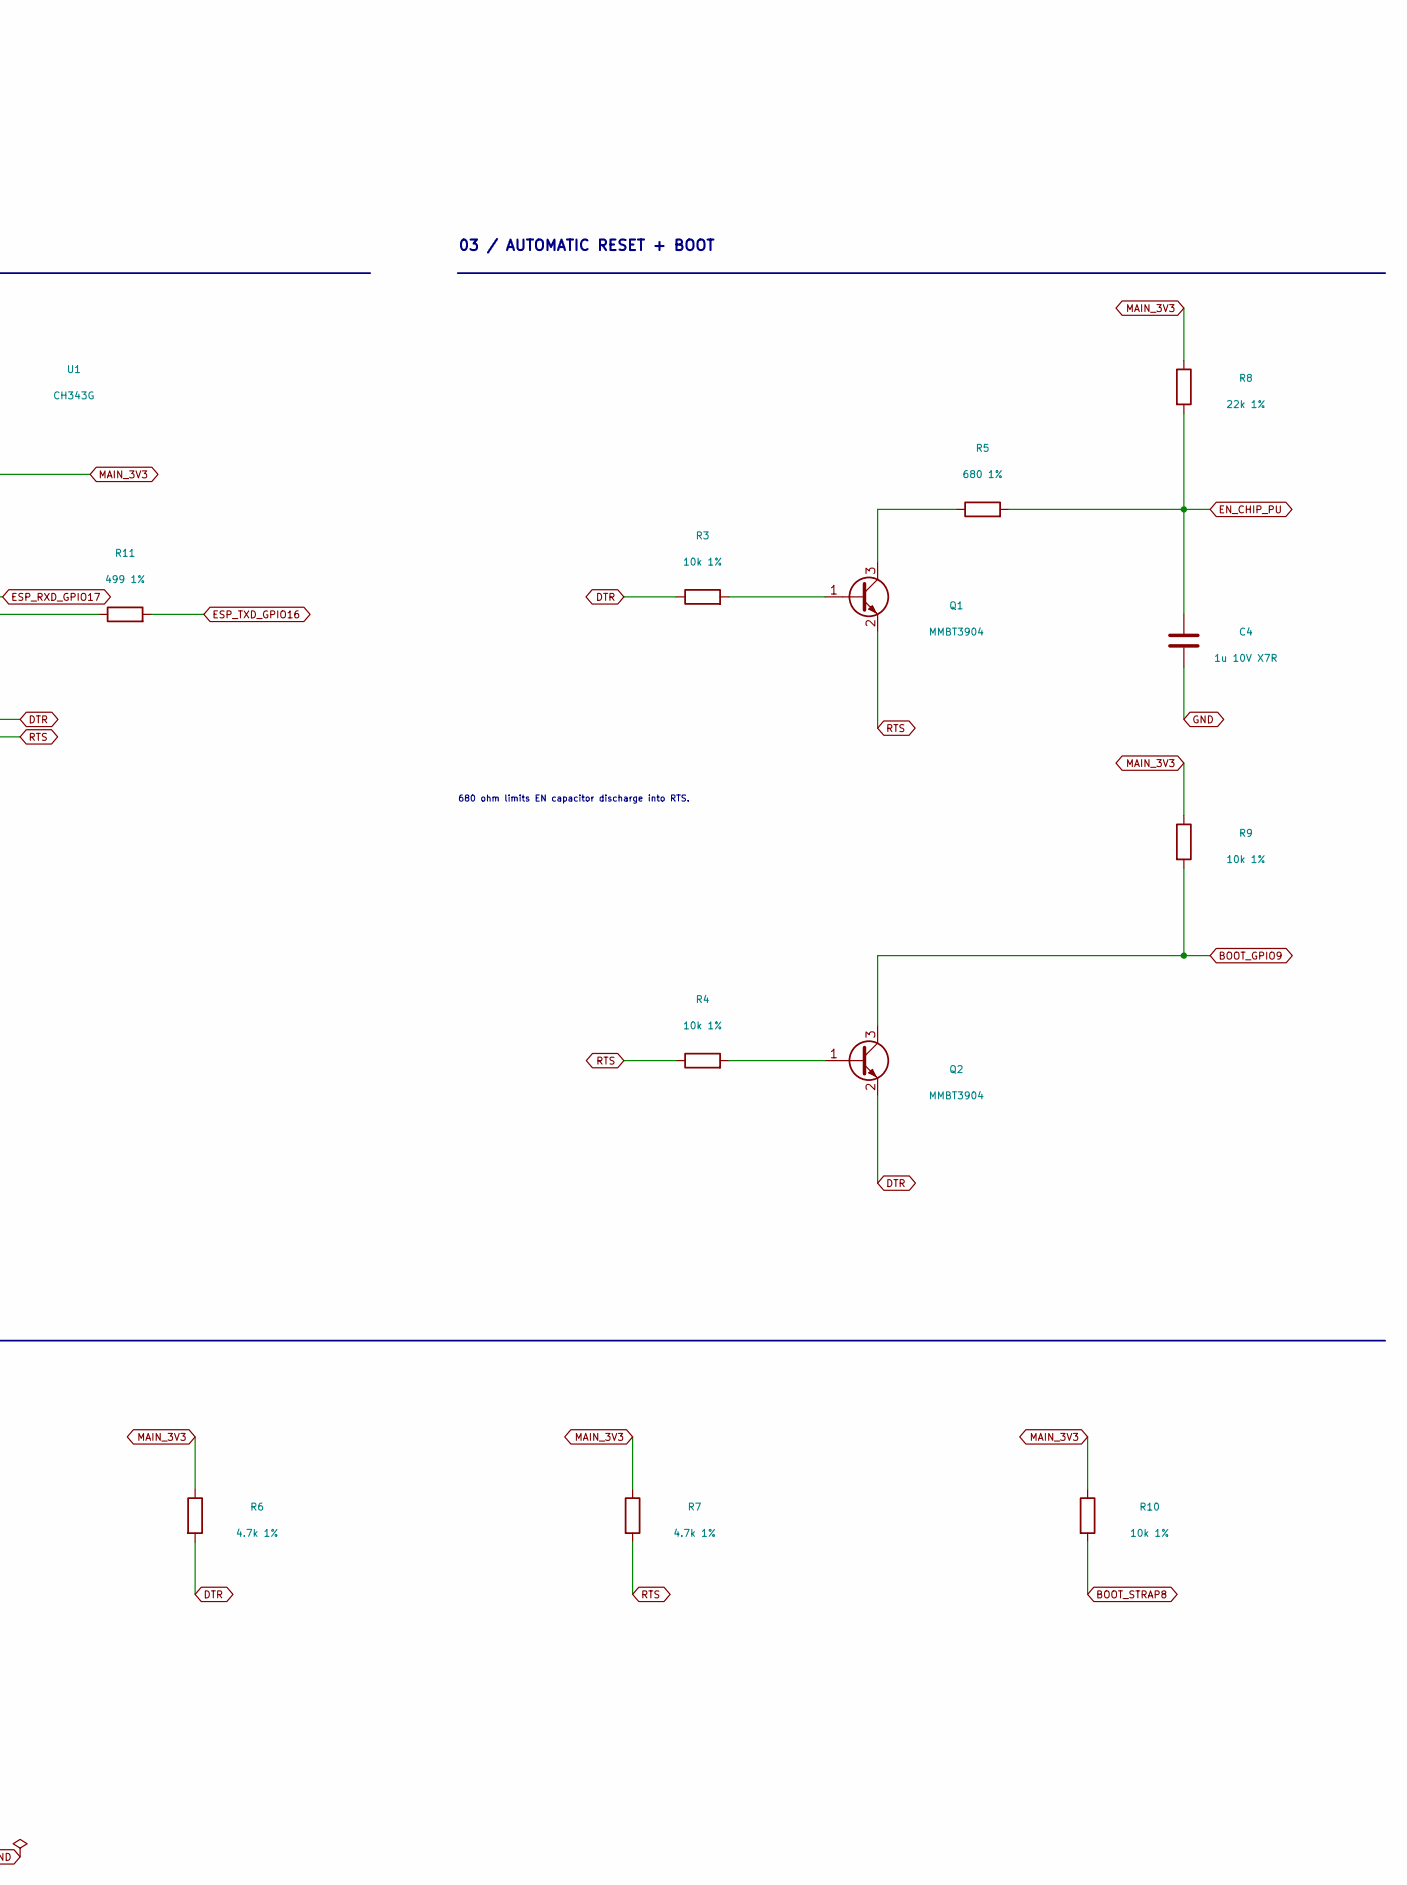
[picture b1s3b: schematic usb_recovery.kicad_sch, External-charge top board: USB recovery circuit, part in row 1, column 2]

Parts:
C1, C2, C3: 100n 50V X7R 10%; C_0603_1608Metric; mpn CC0603KRX7R9BB104; LCSC C14663
C4: 1u 10V X7R; C_0603_1608Metric
Q1, Q2: MMBT3904; SOT-23
R1, R2: 5.1k 1%; R_0603_1608Metric; mpn 0603WAF5101T5E; LCSC C23186
R3, R4, R9, R10: 10k 1%; R_0603_1608Metric; mpn 0603WAF1002T5E; LCSC C25804
R5: 680 1%; R_0603_1608Metric; mpn 0603WAF6800T5E; LCSC C23228
R6, R7: 4.7k 1%; R_0603_1608Metric; mpn 0603WAF4701T5E; LCSC C23162
R8: 22k 1%; R_0603_1608Metric; mpn 0603WAF2202T5E; LCSC C31850
R11: 499 1%; R_0603_1608Metric
U1: CH343G; SOIC-16_3.9x9.9mm_P1.27mm; LCSC C2844153
U2: USBLC6-2SC6; SOT-23-6; mpn USBLC6-2SC6; LCSC C7519
USB1: TYPE-C-31-M-12; USB1_USB-C_SMD-TYPE-C-31-M-12_1; LCSC C165948

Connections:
BOOT_GPIO9: Q2.3 (C), R9.2; also elsewhere on the board
BOOT_STRAP8: R10.2; also elsewhere on the board
CC1: R1.1, USB1.A5 (CC1)
CC2: R2.1, USB1.B5 (CC2)
DTR: Q2.2 (E), R3.1, R6.2, U1.10 (~DTR)
EN_CHIP_PU: C4.1, R5.2, R8.2; also elsewhere on the board
ESP_RXD_GPIO17: U1.2 (TXD); also elsewhere on the board
ESP_TXD_GPIO16: R11.2; also elsewhere on the board
GND: C1.2, C2.2, C3.2, C4.2, R1.2, R2.2, U1.1 (GND), U2.2 (GND), USB1.1 (GND / shell), USB1.2 (GND / shell), USB1.3 (GND / shell), USB1.4 (GND / shell), USB1.A1B12 (GND / shell), USB1.B1A12 (GND / shell); also elsewhere on the board
MAIN_3V3: C3.1, R6.1, R7.1, R8.1, R9.1, R10.1, U1.15 (VIO); also elsewhere on the board
unnamed: Q1.1 (B), R3.2
unnamed: Q1.3 (C), R5.1
unnamed: Q2.1 (B), R4.2
unnamed: R11.1, U1.3 (RXD)
RTS: Q1.2 (E), R4.1, R7.2, U1.11 (~RTS)
USB_D_N: U1.6 (UD-), U2.3 (I/O2), U2.4 (I/O2), USB1.A7 (D-), USB1.B7 (D-)
USB_D_P: U1.5 (UD+), U2.1 (I/O1), U2.6 (I/O1), USB1.A6 (D+), USB1.B6 (D+)
USB_V3: C2.1, U1.4 (V3)
VBUS_RAW: C1.1, U1.7 (VBUS), U1.16 (VDD5), U2.5 (VBUS), USB1.A4B9 (VBUS), USB1.B4A9 (VBUS); also elsewhere on the board

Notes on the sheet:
WHITEBOARDBOT / EXTERNAL-CHARGE REVISION
USB DATA + AUTOMATIC EN / BOOT RECOVERY
TOP-BOARD INTEGRATION - ESP32 ON PAGE 2; SUPPLY CANDIDATE ON PAGE 6
01 / USB-C + DATA PROTECTION
02 / DUAL-SUPPLY USB-UART
03 / AUTOMATIC RESET + BOOT
VDD5 / VBUS: USB only. VIO: same 3.3V rail as ESP32.
No D+/D- series resistors; internal USB pull-up.
No pull-down on DTR: it selects TNOW at power-up.
UART flow control must be disabled for reset service.
680 ohm limits EN capacitor discharge into RTS.
04 / LOCAL BYPASS + DEFINED IDLE LEVELS
External supplies: MAIN_3V3 = regulated ESP32 rail; VBUS_RAW = USB VBUS. Flags are interface assumptions.
No battery charger, balancing, GPIO expander or separate signal isolation ICs on this sheet.
Both DTR/RTS LOW or HIGH -> EN and BOOT HIGH. GPIO8 must stay HIGH for UART ROM download.
